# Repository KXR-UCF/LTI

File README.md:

<div align="center">

  <h1>LTI - Launch &amp; Test Infrastructure</h1>
</div>

LTI is the KXR team responsible for launch and test infrastructure. This
repository contains the software and hardware files used by the WANDA and COSMO
systems.

## System Overview

| System | Location | Deascription |
|--------|----------|-------------|
| **TBA** | [`TBA/`](TBA/README.md) | Runs downrange on Raspberry Pis. Handles relay control. |
| **TBA** | [`TBA/`](TBA/README.md) | Runs at the uprange control station. Sends control commands to TBA. |

---

## Repository Structure

```text
TBA
```

---

## Architecture

TBA

---

## Helpful Resources

+ The test stand uses custom KXR Raspberry Pi hats built around the ADS1256 24-bit ADC. Hardware design files (KiCad schematics, gerbers, BOM) are located in [KXR-UCF/ADS1256-Pi-Hat](https://github.com/KXR-UCF/ADS1256-Pi-Hat).

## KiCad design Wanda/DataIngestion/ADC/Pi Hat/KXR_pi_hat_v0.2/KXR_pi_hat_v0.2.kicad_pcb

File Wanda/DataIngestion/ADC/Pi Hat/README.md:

# ADS1256 Pi Hat

PCB designed and documented by [Ethan Voth](https://github.com/evoth)

A simple PCB to interface up to four load cells with a Raspberry Pi using [this HiLetgo ADS1256 board](https://www.amazon.com/HiLetgo-ADS1256-Acquisition-Precision-Collecting/dp/B09KGXC44Q) and four [JST S4B-XH-A connectors](https://www.digikey.com/en/products/detail/jst-sales-america-inc/S4B-XH-A/1651041). Includes solder bridges to select separate data lines (DRDY, CS, PDWN) when connecting two boards at the same time.

This board will be used to facilitate high-speed data acquisition for rocket motor static fires, interfacing with multiple load cells and possibly a pressure transducer (PT). Data acquisition is a key responsibility of the Knights Experimental Rocketry (KXR) Launch Test Infrastructure (LTI) team, which provides test stands and data for multiple rocketry teams within KXR.

Since this is the third PCB I've ever designed (I'm a CS major with only self-taught electronics knowledge), there are certainly improvements to be made. Ground plane, separate analog ground, sources of noise, and filtering for analog lines would be good areas of learning for a future version of this board.

## Files

The KiCad project (including schematic, board, and fabrication files) can be found in the `KXR_pi_hat_v0.2` directory.

(Ignore `KXR_pi_hat_v0.1`, which was an... interesting idea to cram 5 independent HX711 modules onto 2 boards with a single design.)

## Parts

### [HiLetgo ADS1256 Board](https://www.amazon.com/HiLetgo-ADS1256-Acquisition-Precision-Collecting/dp/B09KGXC44Q)

This HiLetgo module contains support components for the [ADS1256 ADC](https://www.ti.com/lit/ds/symlink/ads1255.pdf?ts=1750027613648) and breaks out the analog inputs and data lines. Since we only need one or two of these for our application, it made more sense to use a ready-made module than trying to integrate the raw ADC chip.

**Pins**

- **5V, GND**: Power for the board. There are also separate analog grounds which were tied to the same GND for this design.
- **SCLK, DIN, DOUT**: SPI bus for communication between the Pi and ADS1256 to change settings and read data. Can be shared between multiple modules.
- **CS, DRDY, PDWN**: Additional lines for signalling during data transmission. Need to be connected to separate pins for each module.
- **AIN0-AIN7**: Analog inputs for voltage measurement. These pins can either act as 8 single-ended inputs or 4 differential inputs. Load cells give a differential signal.

### JST S4B-XH-A Connectors

These are standard 2.5mm right-angle connectors, which were selected because 2.5mm JST connectors had been used to connect load cells in previous designs.

Below is the wiring convention used in this design:

- **Pin 1**: GND/Excitation- (black)
- **Pin 2**: Signal- (white)
- **Pin 3**: Signal+ (green)
- **Pin 4**: 5V/Excitation+ (red)

### [Stacking Headers](https://www.amazon.com/Female-Stacking-Header-Compatible-Raspberry/dp/B084Q4W1PW)

We used stacking headers to allow another board to be stacked on top, but any 2x20 2.54mm pitch female headers should work for attaching the PCB to the Pi.

## Assembly

### 1. Solder headers

The headers for connecting to the Pi should be soldered first, because otherwise the ADS1256 board might get in the way. Make sure the female side is facing down (towards side with KXR logo).

### 2. Solder ADS1256 module

Solder the ADS1256 module onto the top of the board, lined up with the footprint. **It will not work if soldered on the other side!**

### 3. Solder JST connectors

Same deal, solder the connectors as marked on the PCB.

### 4. Bridge solder jumpers

Select pins for DRDY, CS, and PDWN using solder jumpers on the back of the board. By bridging either the left or right pads with the center pads, corresponding pins from the ADS1256 module can be connected to one of two different pins on the Pi. See the [Jumpers](#jumpers) section for more details.

## Schematic

This should be pretty self-explanatory. J1 is connected to AIN0/1, J2 is connected to AIN2/3, etc., and the SPI lines are connected to the hardware SPI on the Pi. The solder jumpers are the only thing to watch out for.

## Jumpers

To use two boards at the same time, they will need to have separate data lines. To do this, bridge the solder jumpers on the right side for "Board 1", and the left side for "Board 2".

### "Board 1" pins:

| Pin      | GPIO   | Physical Pin # |
| -------- | ------ | -------------- |
| **DRDY** | GPIO22 | 15             |
| **CS**   | GPIO8  | 24             |
| **PDWN** | GPIO24 | 18             |

### "Board 2" pins:

| Pin      | GPIO   | Physical Pin # |
| -------- | ------ | -------------- |
| **DRDY** | GPIO23 | 16             |
| **CS**   | GPIO7  | 26             |
| **PDWN** | GPIO25 | 22             |

## Software

To use the ADS1256, find an applicable library, modifying it as needed. For example, you could clone [this repo for Waveshare boards](https://github.com/waveshareteam/High-Precision-AD-DA-Board/tree/master/RaspberryPI/ADS1256/python3) and modify `config.py` with the applicable pin numbers. This library is slightly broken as it does not support differential mode. This can be fixed by changing the global ScanMode variable to an [instance variable](https://docs.python.org/3/tutorial/classes.html#class-and-instance-variables) in the ADS1256 class in the ADS1256.py module. Additionally the ScanMode variable should be set to 1 for differential mode.

The raspberry pi 5 no longer supports the [`RPi.GPIO` Library](https://pypi.org/project/RPi.GPIO/). Instead install the [`rpi-lgpio` Library](https://pypi.org/project/rpi-lgpio/). This library does not need any of the python code to be changed (this includes the import statement).

One issue you may run into is the fact that the board uses the hardware CS pin, which is often claimed by the SPI interface, so it can't be used as a GPIO output. Since most ADS1256 libraries will manually set the CS pin, you will need to free up the pin to be used as an output. This can be done by changing the SPI device tree overlay to one which doesn't claim the CS pin, such as `spi0-0cs`. To do this, add the line `dtoverlay=spi0-0cs` to `/boot/firmware/config.txt` (or `/boot/firmware/config.txt` on older versions), removing any conflicting dtoverlays if necessary (comment out `dtparam=spi=on`).

Good luck!

## Pictures

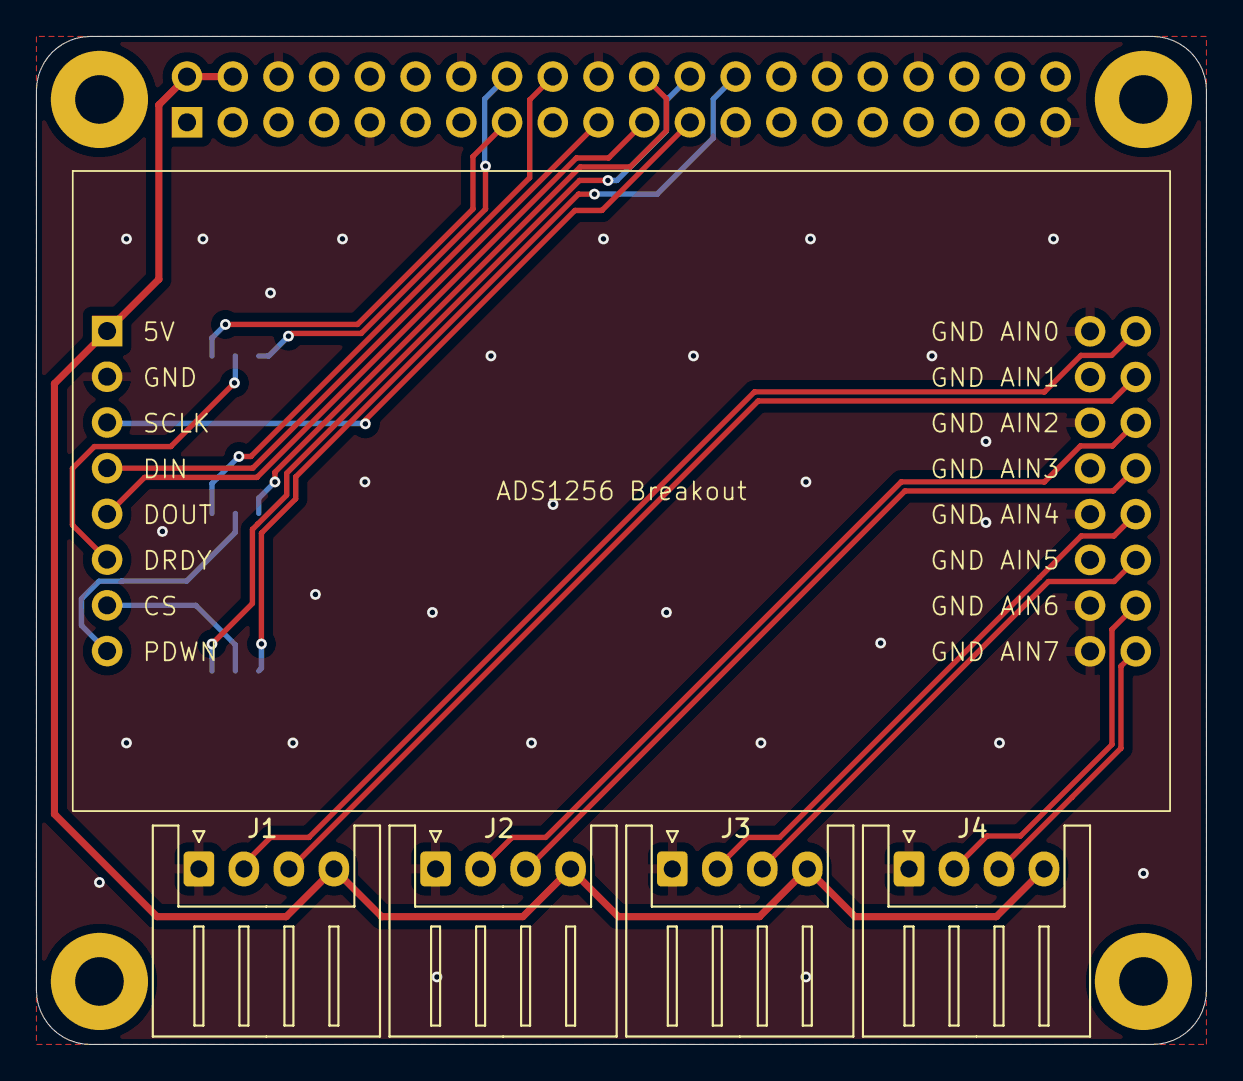
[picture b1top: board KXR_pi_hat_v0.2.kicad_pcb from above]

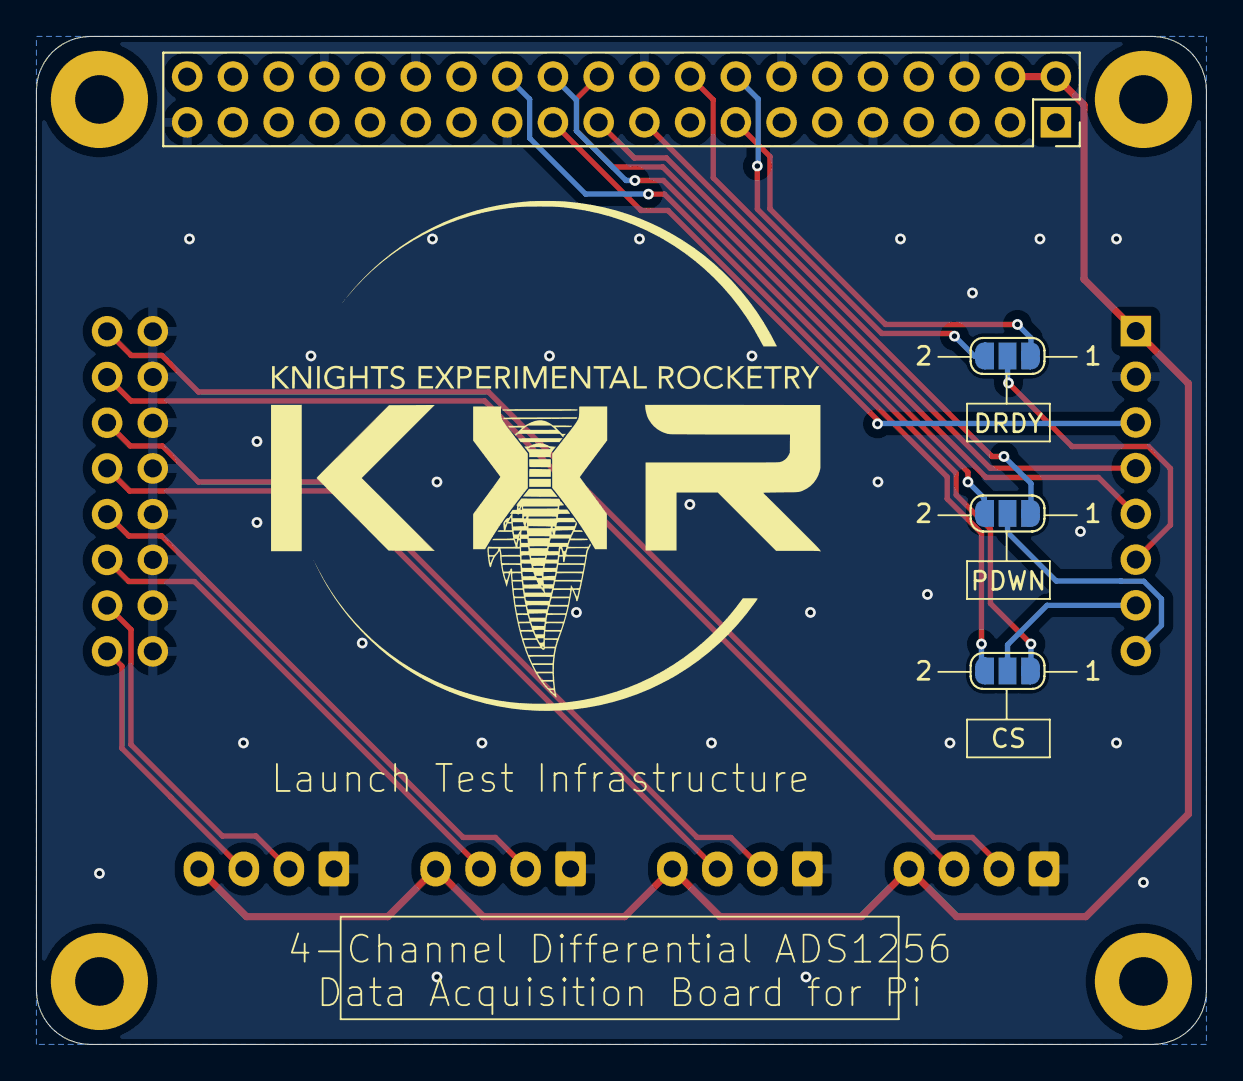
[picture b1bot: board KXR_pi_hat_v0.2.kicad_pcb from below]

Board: 2 copper layers, 65.0 x 56.0 mm, 9 parts (4 on the bottom side), 22 nets.

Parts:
ADS1256 Breakout: HiLetGo_ADS1256
CS: SolderJumper_3_Open; SolderJumper-3_P1.3mm_Open_RoundedPad1.0x1.5mm_NumberLabels
DRDY: SolderJumper_3_Open; SolderJumper-3_P1.3mm_Open_RoundedPad1.0x1.5mm_NumberLabels
J1, J2, J3, J4: Conn_01x05_Pin; JST_XH_S4B-XH-A_1x04_P2.50mm_Horizontal
PDWN: SolderJumper_3_Open; SolderJumper-3_P1.3mm_Open_RoundedPad1.0x1.5mm_NumberLabels
U1: Raspberry_Pi_2_3; PinSocket_2x20_P2.54mm_Vertical

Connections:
+5V: ADS1256 Breakout.1 (5V), J1.4, J2.4, J3.4, J4.4, U1.2 (5V), U1.4 (5V)
/CS_1: CS.1 (A), U1.24 (~CE0/GPIO8)
/CS_2: CS.3 (B), U1.26 (~CE1/GPIO7)
/DRDY_1: DRDY.1 (A), U1.15 (GPIO22)
/DRDY_2: DRDY.3 (B), U1.16 (GPIO23)
/LC1_S+: ADS1256 Breakout.12 (AIN1), J1.3
/LC1_S-: ADS1256 Breakout.10 (AIN0), J1.2
/LC2_S+: ADS1256 Breakout.16 (AIN3), J2.3
/LC2_S-: ADS1256 Breakout.14 (AIN2), J2.2
/LC3_S+: ADS1256 Breakout.20 (AIN5), J3.3
/LC3_S-: ADS1256 Breakout.18 (AIN4), J3.2
/LC4_S+: ADS1256 Breakout.24 (AIN7), J4.3
/LC4_S-: ADS1256 Breakout.22 (AIN6), J4.2
/MISO: ADS1256 Breakout.5 (DOUT), U1.21 (MISO0/GPIO9)
/MOSI: ADS1256 Breakout.4 (DIN), U1.19 (MOSI0/GPIO10)
/PDWN_1: PDWN.1 (A), U1.18 (GPIO24)
/PDWN_2: PDWN.3 (B), U1.22 (GPIO25)
/SCLK: ADS1256 Breakout.3 (SCLK), U1.23 (SCLK0/GPIO11)
GND: ADS1256 Breakout.2 (GND), ADS1256 Breakout.9 (GND), ADS1256 Breakout.11 (GND), ADS1256 Breakout.13 (GND), ADS1256 Breakout.15 (GND), ADS1256 Breakout.17 (GND), ADS1256 Breakout.19 (GND), ADS1256 Breakout.21 (GND), ADS1256 Breakout.23 (GND), J1.1, J2.1, J3.1, J4.1, U1.6 (GND), U1.9 (GND), U1.14 (GND), U1.20 (GND), U1.25 (GND), U1.30 (GND), U1.34 (GND), U1.39 (GND)
unnamed: ADS1256 Breakout.6 (DRDY), DRDY.2 (C)
unnamed: ADS1256 Breakout.7 (CS), CS.2 (C)
unnamed: ADS1256 Breakout.8 (PDWN), PDWN.2 (C)

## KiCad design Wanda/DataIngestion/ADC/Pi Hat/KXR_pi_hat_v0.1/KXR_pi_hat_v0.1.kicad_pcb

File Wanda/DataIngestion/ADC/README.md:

# ADC

This folder contains the ADS1256 library and the DAQ manager module to interface with the ADS1256 Pi Hats on the Raspberry Pis

## Files
 
| File | Description |
|---|---|
| [`ADS1256.py`](ADS1256.py) | Low-level SPI library for the ADS1256 ADC |
| [`adcmanager.py`](adcmanager.py) | High-level DAQ and Sensor manager, configured via YAML |

## ADS1256.py

This library is a modified version of the library from [this repo for Waveshare boards](https://github.com/waveshareteam/High-Precision-AD-DA-Board/tree/master/RaspberryPI/ADS1256/python3).

**Modifications**
- Added `scan_mode` instance variable to properly support differential mode (`setMode()` was previously not working)
- Supports multiple instances of the ADS1256 with seperate pin numbers.

### Setup

The raspberry pi 5 no longer supports the [`RPi.GPIO` Library](https://pypi.org/project/RPi.GPIO/). Instead install the [`rpi-lgpio` Library](https://pypi.org/project/rpi-lgpio/). This library does not need any of the python code to be changed (this includes the import statement).

To use the library on a raspberry pi add the line `dtoverlay=spi0-0cs` to `/boot/firmware/config.txt` (or `/boot/firmware/config.txt` on older versions), removing any conflicting dtoverlays if necessary (comment out `dtparam=spi=on`). A longer explanation why this change is needed can be found in the [Pi Hat Folder](Pi%20Hat/).

### Usage

Declare an instance of the ADS1256 class with the pins for the ADC (for pin numbers refer to the [Pi Hat README](Pi%20Hat#jumpers)).

Example:
```python
from ADS1256 import ADS1256, GAIN_E, DRATE_E

adc = ADS1256(rst_pin=24, cs_pin=8, drdy_pin=22)
adc.init()
adc.configADC(GAIN_E['GAIN_2'], DRATE_E['3750SPS'])
adc.setMode(0) # 0 = single-ended (8 ch), 1 = differential (4 ch)

voltage = adc.getChannelVoltage(channel=0)
```

An additional example file is provided in [`4chdiff.py`](4chdiff.py)

#### Functions

| Function | Description |
|---|---|
| `init()` | Initializes GPIO/SPI, resets chip, and verifies chip ID. Applies a default config. **Must be called before any other function can work** |
| `configADC(gain, dataRate)` | Change the PGA gain or data rate. Acceptable parameters can be found at the top of [`ADS1256.py`](ADS1256.py) in `GAIN_E` and `DRATE_E`. |
| `setMode(mode)` | `0` = single-ended (8 channels), `1` = differential (4 channels, default). |
| `getChannelValue(channel)` | Get the output value of a specific channel. The returned value is the raw 24-but reading of a channel. This output value is not directly equal to the voltage. |
| `getChannelVoltage(self, channel, Vref=2.5)` | Get the output voltage of a specific channel. In differential mode: channels 0-3. In single ended mode: chanmels: 0-7. **Primary function for retrieving information from sensor channels** |
| `readChipID()` | Reads the chip ID of the ADS1256. Returns `3` if ADS1256 is healthy/connected |
| `module_exit()` | Cleans GPIO and closes SPI. Recomeneded to call on shutdown |

**Available Gain Settings (`GAIN_E`):** `GAIN_1`, `GAIN_2`, `GAIN_4`, `GAIN_8`, `GAIN_16`, `GAIN_32`, `GAIN_64`
 
**Available Data Rates (`DRATE_E`):** `30000SPS`, `15000SPS`, `7500SPS`, `3750SPS`, `2000SPS`, `1000SPS`, `500SPS`, `100SPS`, `60SPS`, `50SPS`, `30SPS`, `25SPS`, `15SPS`, `10SPS`, `5SPS`, `2d5SPS`

---

## adcmanager.py

DAQ manager that wraps `ADS1256.py`. Reads a YAML config file to initialize ADCs and map named sensors to specific channels, additionally handles sensor calibration values.

### Usage
 
```python
from adcmanager import DAQ
 
with DAQ("config.yaml") as daq:
    values = daq.get_all_sensor_values()
    print(values)  # {'pt1': 245.3, 'pt2': 118.7, ...}
```

Using `DAQ` as a context manager (`with` statement) is recommended since it runs a health check on startup and calls `cleanup()` on exit.

### Config File
 
The config file is a YAML file with two top-level sections: ADC hardware configuration and sensor definitions.
 
```yaml
ADC1:
  enabled: true
  differential: false       # true = differential mode (4 ch), false = single-ended (8 ch)
  gain: "GAIN_2"            # See GAIN_E in ADS1256.py
  data_rate: "3750SPS"      # See DRATE_E in ADS1256.py
  RST_PIN: 24               # BCM pin numbers
  CS_PIN: 8
  DRDY_PIN: 22
  channels:
    0: "pt2"                # Map channel index to sensor name (must match a key under `sensors`)
    1: "pt1"
    2: null                 # Unmapped channels should be set to null
 
ADC2:
  enabled: true
  differential: false
  gain: "GAIN_1"
  data_rate: "3750SPS"
  RST_PIN: 25
  CS_PIN: 7
  DRDY_PIN: 23
  channels:
    0: "pt3"
    1: "continuity_raw"
    2: null
 
sensors:
  pt1:
    zero: -1031.4           # Voltage offset (additive, applied after scale)
    scale: 3071.4           # Volts-to-engineering-units scale factor
  pt2:
    zero: -283.77
    scale: 918.83
  pt3:
    zero: null              # A null zero defaults to 0
    scale: null             # A null scale defaults to 1
  continuity_raw:
    zero: 0
    scale: 1
```

**Calibration formula:** `calibrated_value = voltage × scale + zero`
 
Sensor names used in the `channels` map must have a corresponding entry under `sensors`. Channels set to `null` are ignored

### DAQ Class
 
| Method | Description |
|---|---|
| `DAQ(config_filename)` | Loads config, initializes enabled ADCs, and registers all sensors. |
| `get_all_sensor_values()` | Returns a `dict` of `{sensor_name: calibrated_value}` for all configured sensors. |
| `get_sensor_names()` | Returns a list of all configured sensor names. |
| `get_sensor_dict()` | Returns the `{name: Sensor}` dictionary. |
| `check_health(retries=1)` | Reads chip ID from each ADC. Attempts re-initialization on failure. Returns `True` if all ADCs are healthy. |
| `cleanup()` | Releases GPIO and SPI resources. Called automatically when used as a context manager. |
 
### Sensor Class
 
`Sensor` objects are created automatically by `DAQ` during config loading. They can also be created manually via `daq.create_sensor(sensor_name)`.
 
| Method | Description |
|---|---|
| `get_voltage()` | Returns the raw voltage from the sensor's ADC channel. |
| `get_calibrated_value_linear()` | Returns `voltage × scale + zero` using values from the config. |
 
---

## Example Scripts
 
The following scripts are development and calibration utilities. They are not part of the data ingestion and are not intended for production.
 
| File | Description |
|---|---|
| `4chdiff.py` | Basic example reading 4 differential channels in a loop and printing voltages. |
| `calibration.py` | Reads all channels and prints a rolling average, useful for determining `scale` and `zero` values for the config file. Supports both single-ended and differential mode via the `DIFFERENTIAL` flag. |
| `livechannels.py` | Same as `calibration.py` but without averaging — prints raw per-sample values. Useful for checking noise and live sensor response. |
 
---
 
## Helpful Resources
 
- [ADS1256 Datasheet](https://www.ti.com/product/ADS1256)
- [Waveshare High-Precision AD/DA Board](https://github.com/waveshareteam/High-Precision-AD-DA-Board)
- [`rpi-lgpio` (Pi 5 GPIO replacement)](https://pypi.org/project/rpi-lgpio/)

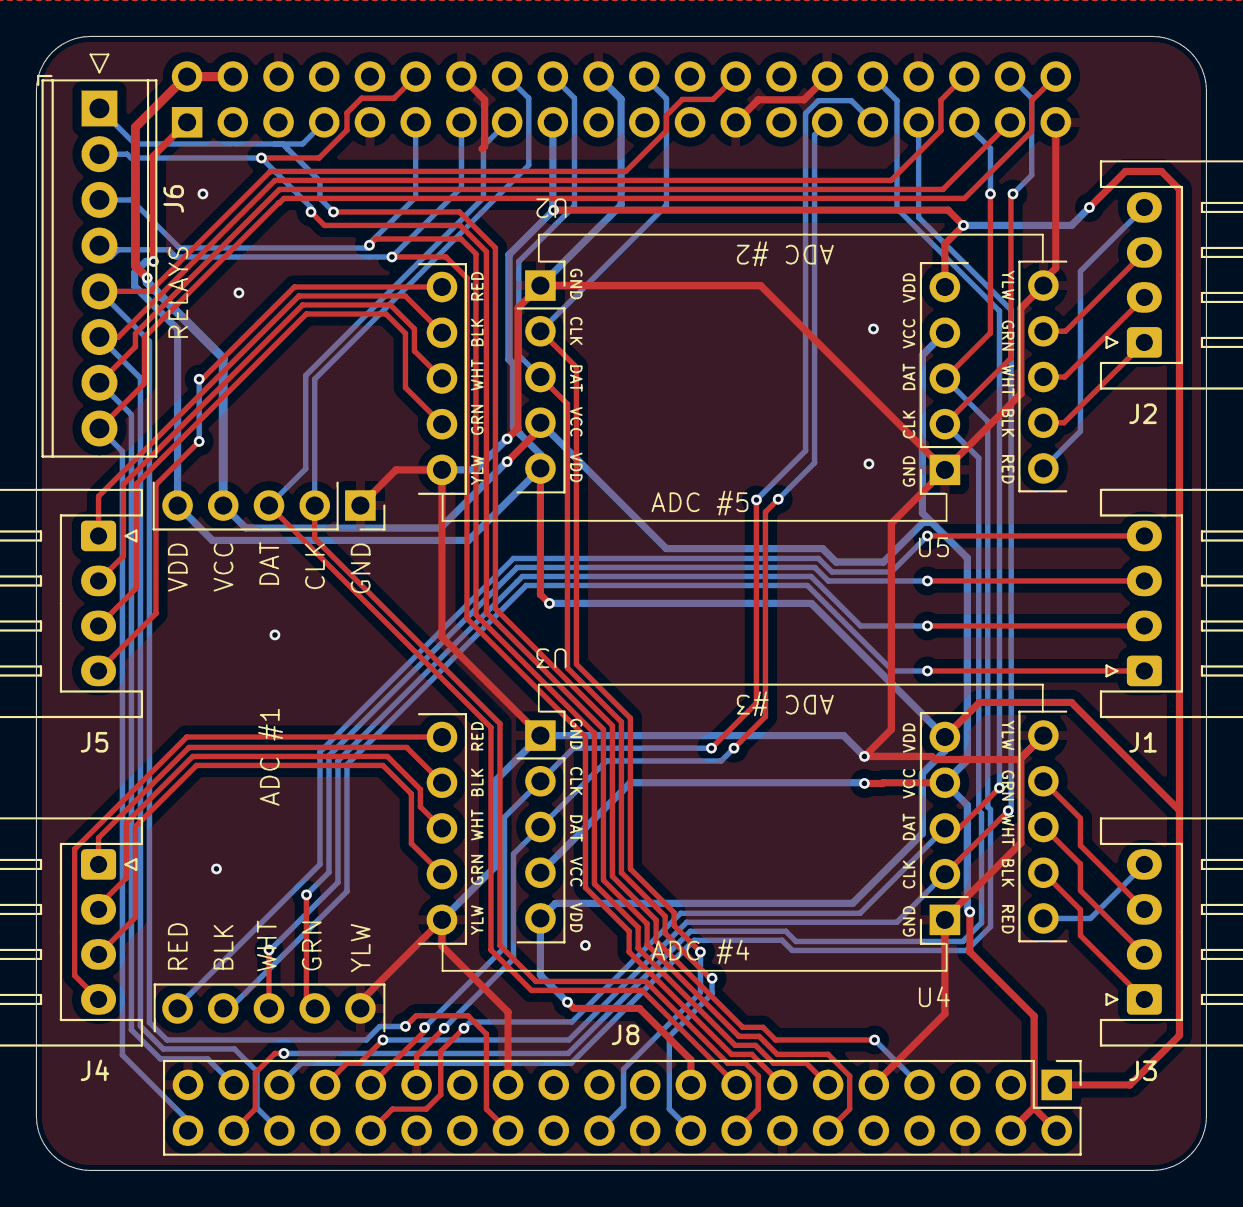
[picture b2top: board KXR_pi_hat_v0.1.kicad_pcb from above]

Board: 2 copper layers, 65.0 x 63.0 mm, 13 parts (1 on the bottom side), 41 nets.

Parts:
J1, J2, J3, J4, J5: Conn_01x04_Pin; JST_XH_S4B-XH-A_1x04_P2.50mm_Horizontal
J6: Conn_01x08_Pin; TerminalBlock_Phoenix_MPT-0,5-8-2.54_1x08_P2.54mm_Horizontal
J7, J8: Raspberry_Pi_2_3; PinSocket_2x20_P2.54mm_Vertical
U1: HX711_Load_Cell_Amp_PinSocket_basic
U2, U3, U4, U5: HX711_Load_Cell_Amp_PinSocket_basic2

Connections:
+3V3: J7.1 (3V3), J7.17 (3V3), J8.1 (3V3), J8.17 (3V3), U1.5 (VDD), U2.5 (VDD), U3.5 (VDD), U4.5 (VDD), U5.5 (VDD)
+5V: J7.2 (5V), J7.4 (5V), J8.2 (5V), J8.4 (5V), U1.4 (VCC), U2.4 (VCC), U3.4 (VCC), U4.4 (VCC), U5.4 (VCC)
/ADC1_CLK: J7.16 (GPIO23), J8.16 (GPIO23), U1.2 (CLK)
/ADC1_DAT: J7.15 (GPIO22), J8.15 (GPIO22), U1.3 (DAT)
/ADC2_CLK: J7.22 (GPIO25), J8.22 (GPIO25), U2.2 (CLK)
/ADC2_DAT: J7.18 (GPIO24), J8.18 (GPIO24), U2.3 (DAT)
/ADC3_CLK: J7.31 (GCLK2/GPIO6), J8.31 (GCLK2/GPIO6), U3.2 (CLK)
/ADC3_DAT: J7.29 (GCLK1/GPIO5), J8.29 (GCLK1/GPIO5), U3.3 (DAT)
/ADC4_CLK: J7.33 (PWM1/GPIO13), J8.33 (PWM1/GPIO13), U4.2 (CLK)
/ADC4_DAT: J7.32 (PWM0/GPIO12), J8.32 (PWM0/GPIO12), U4.3 (DAT)
/ADC5_CLK: J7.38 (GPIO20/MOSI1), J8.38 (GPIO20/MOSI1), U5.2 (CLK)
/ADC5_DAT: J7.35 (GPIO19/MISO1), J8.35 (GPIO19/MISO1), U5.3 (DAT)
/RLY1: J6.1, J7.7 (GCLK0/GPIO4), J8.7 (GCLK0/GPIO4)
/RLY2: J6.2, J7.12 (GPIO18/PWM0), J8.12 (GPIO18/PWM0)
/RLY3: J6.3, J7.11 (GPIO17), J8.11 (GPIO17)
/RLY4: J6.4, J7.13 (GPIO27), J8.13 (GPIO27)
/RLY5: J6.5, J7.26 (~CE1/GPIO7), J8.26 (~CE1/GPIO7)
/RLY6: J6.6, J7.36 (GPIO16), J8.36 (GPIO16)
/RLY7: J6.7, J7.37 (GPIO26), J8.37 (GPIO26)
/RLY8: J6.8, J7.40 (GPIO21/SCLK1), J8.40 (GPIO21/SCLK1)
GND: J7.6 (GND), J7.9 (GND), J7.14 (GND), J7.20 (GND), J7.25 (GND), J7.30 (GND), J7.34 (GND), J7.39 (GND), J8.6 (GND), J8.9 (GND), J8.14 (GND), J8.20 (GND), J8.25 (GND), J8.30 (GND), J8.34 (GND), J8.39 (GND), U1.1 (GND), U1.10 (YLW), U2.1 (GND), U2.10 (YLW), U3.1 (GND), U3.10 (YLW), U4.1 (GND), U4.10 (YLW), U5.1 (GND), U5.10 (YLW)
unnamed: J1.1, U1.7 (BLK)
unnamed: J1.2, U1.8 (WHT)
unnamed: J1.3, U1.9 (GRN)
unnamed: J1.4, U1.6 (RED)
unnamed: J2.1, U2.7 (BLK)
unnamed: J2.2, U2.8 (WHT)
unnamed: J2.3, U2.9 (GRN)
unnamed: J2.4, U2.6 (RED)
unnamed: J3.1, U3.7 (BLK)
unnamed: J3.2, U3.8 (WHT)
unnamed: J3.3, U3.9 (GRN)
unnamed: J3.4, U3.6 (RED)
unnamed: J4.1, U4.7 (BLK)
unnamed: J4.2, U4.8 (WHT)
unnamed: J4.3, U4.9 (GRN)
unnamed: J4.4, U4.6 (RED)
unnamed: J5.1, U5.7 (BLK)
unnamed: J5.2, U5.8 (WHT)
unnamed: J5.3, U5.9 (GRN)
unnamed: J5.4, U5.6 (RED)

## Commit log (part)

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2025-09-19 Initial commit: LTI 25 telemetry system with frontend UIs and data processing
2025-10-17 reorganized WANDA code
2025-10-17 Fix note formatting in README.md
    Updated note formatting in README for clarity.
2025-11-01 Revise README for Python and QuestDB setup instructions (#3)
    Updated instructions for setting up Python environment on the Pi 5
2025-11-11 Relay mapping (#7)
    * updated README.md
    * set up control mapping
    * fixed import statement
    * added success check
    * set up response check
    * set up worker client
2025-11-11 fixed config file paths (#8)
2025-11-14 Relay mapping bug fixes (#10)
    * updated README.md
    * set up control mapping
    * fixed import statement
    * added success check
    * set up response check
    * set up worker client
2025-11-16 Relay mapping new (#14)
    * updated README.md
    * set up control mapping
    * fixed import statement
    * added success check
    * set up response check
    * set up worker client
2025-11-23 Relay mapping Fixes (#17)
    * updated README.md
    * set up control mapping
    * fixed import statement
    * added success check
    * set up response check
    * set up worker client
2025-11-25 fixed clients connection (#21)
2025-12-08 started status server
2025-12-08 Added automatic wanda script
2025-12-08 autostart added
2025-12-09 Added autostart (#23)
    * started status server
    * Added automatic wanda script
    * autostart added
    ---------
2026-01-20 added file viewing
2026-01-20 set up error checking
2026-01-20 typo
2026-01-21 refactored for modularity
2026-01-22 set up command overrides
2026-01-27 cleanup
2026-01-27 fixed abort rejecting turning off relays
2026-01-27 set up multithread
2026-02-03 fixed some bugs
2026-02-03 Adcmanager updates (#24)
2026-02-03 Controls timings (#25)
2026-02-04 split each part into its own service with error handling
2026-02-05 fixed timezone
2026-02-08 fixed controls
2026-02-08 split each part into its own service with error handling (#26)
2026-02-08 fixed control controllerSocketServer
2026-02-08 removed debug
2026-02-08 control server fixes from dry dress
2026-02-10 fixed abort
2026-02-24 fixed logging
2026-02-24 data batching
2026-03-04 added services
2026-03-04 improved styling
2026-03-04 added connected messages
2026-03-04 updated log file output paths
2026-03-04 added log file checking
2026-03-04 added timings to logs
2026-03-04 fixed file limit
2026-03-04 added wanda config to git
2026-03-04 added log clearing
2026-03-04 config file and control buttons
2026-03-04 added downloading and adjusted allowed files
2026-03-04 added requirements and pi setup script
2026-03-21 set up hold positions and database
2026-03-23 adjusted hold positions and logic
2026-03-23 small fixes
2026-03-23 updated ingestion
2026-03-24 added comments
2026-03-24 added some more comments
2026-03-31 potential fix for negative numbers
2026-03-31 moved dataingestion into subfolder
2026-04-07 reworked adcmanager with DAQ class
2026-04-07 documentation update
2026-04-07 moved config files
2026-04-07 updated dataingestion to support new adcmanager
2026-04-07 update to newer function
2026-04-07 added info about non production scripts
2026-04-07 fixed path erros
2026-04-07 fixed grafana enabling
2026-04-07 updated queue prints
2026-04-07 fixed cleanup
2026-04-07 Documentation Updates
2026-04-07 Added WANDA documentation
2026-04-07 added links
2026-04-07 updated service documentation
2026-04-07 Update links in README.md for file references
2026-04-07 Update README.md to include file links
2026-04-07 rename
2026-04-07 added controls shutdown
2026-04-13 Refactor relay configurations and enhance fire command logic in overrideCMD.py
2026-04-20 Update service files
2026-04-20 Duplicate wanda status server for cosmo
2026-04-21 Update file paths for kxr computer
2026-04-21 Update cosmo status server
2026-04-21 Move log files to generate in Cosmo directory
2026-04-21 Update paths
2026-04-21 Use complete npm paths
2026-04-21 Add environment for frontend and backend services
2026-04-27 Remove old startup script and service
2026-05-01 Add CODEOWNERS file for repository ownership
2026-05-07 Update quest db host
2026-05-07 Rename status server to wanda status server
2026-05-14 Decreased queue size and adjusted grafana integration
2026-05-14 Adjusted service file paths
2026-05-14 Adjusted paths
2026-05-14 Implemented EMA and moving median to grafana data
2026-05-14 fixed names
2026-05-14 Revert "Wanda cleanup"
2026-05-14 Revert "Merge pull request #57 from KXR-UCF/wanda-cleanup"
    This reverts commit 91228cc73979f0ba900b1b0ee24216c1a55779d7, reversing
    changes made to 37b97d74655c8056c502123729775b276317e494.
2026-05-14 Reapply "Wanda cleanup"
    This reverts commit eef50d60833181c427259b23cde9d3bdeb2e6e51.
